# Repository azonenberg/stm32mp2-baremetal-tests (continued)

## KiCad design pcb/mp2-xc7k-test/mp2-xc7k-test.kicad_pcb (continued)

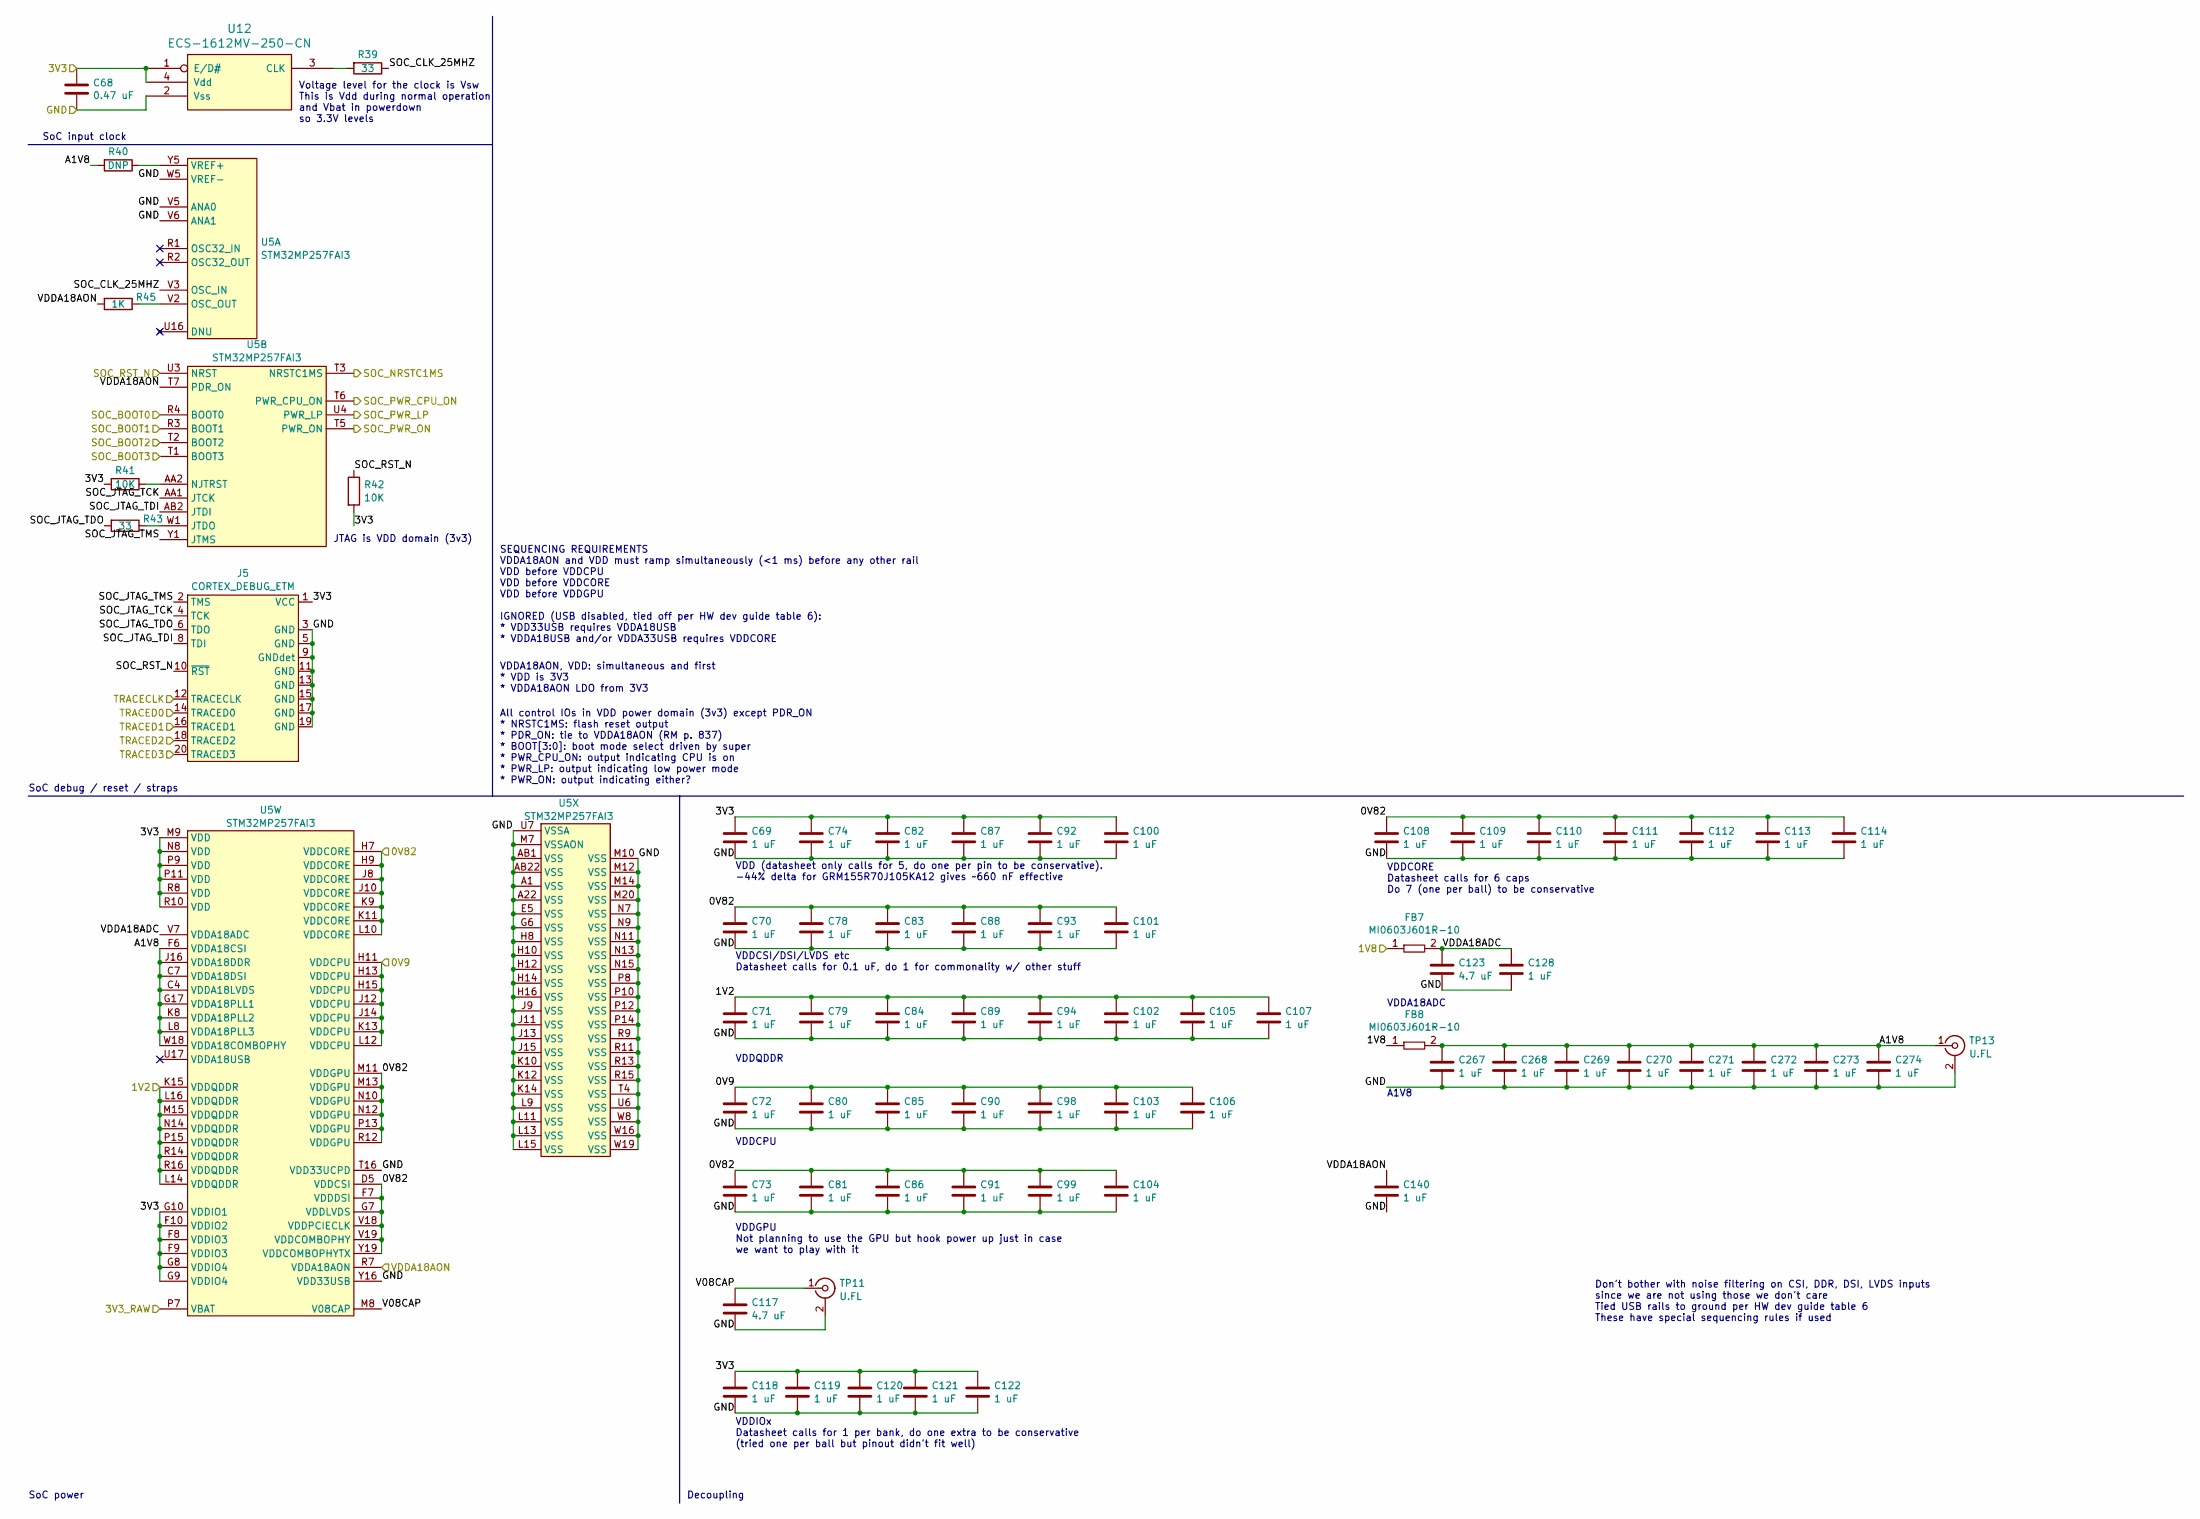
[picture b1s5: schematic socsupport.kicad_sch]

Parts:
C68: 0.47 uF; EIA_0402_CAP_NOSILK
C69, C70, C71, C72, C73, C74, C78, C79, C80, C81, C82, C83, C84, C85, C86, C87, C88, C89, C90, C91, C92, C93, C94, C98, C99, C100, C101, C102, C103, C104, C105, C106, C107, C108, C109, C110, C111, C112, C113, C114, C118, C119, C120, C121, C122, C128, C140, C267, C268, C269, C270, C271, C272, C273, C274: 1 uF; EIA_0201_CAP_NOSILK
C117, C123: 4.7 uF; EIA_0603_CAP_NOSILK
FB7, FB8: MI0603J601R-10; EIA_0603_INDUCTOR_NOSILK
J5: CORTEX_DEBUG_ETM; CONN_HEADER_1.27MM_2x10_SMT_SAMTEC_FTSH-110-01-L-DV-K
R39, R43: 33; EIA_0402_RES_NOSILK
R40: DNP; EIA_0402_RES_NOSILK
R41, R42: 10K; EIA_0402_RES_NOSILK
R45: 1K; EIA_0402_RES_NOSILK
TP11, TP13: U.FL; CONN_U.FL_TE_1909763-1
U5: STM32MP257FAI3; BGA_436_18x18_DEPOP_0.8MM
U12: ECS-1612MV-250-CN; OSCILLATOR_1.6x1.2

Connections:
/0V9: C72.1, C80.1, C85.1, C90.1, C98.1, C103.1, C106.1, U5.H11 (VDDCPU), U5.H13 (VDDCPU), U5.H15 (VDDCPU), U5.J12 (VDDCPU), U5.J14 (VDDCPU), U5.K13 (VDDCPU), U5.L12 (VDDCPU); also elsewhere on the board
/0V82: C70.1, C73.1, C78.1, C81.1, C83.1, C86.1, C88.1, C91.1, C93.1, C99.1, C101.1, C104.1, C108.1, C109.1, C110.1, C111.1, C112.1, C113.1, C114.1, U5.D5 (VDDCSI), U5.F7 (VDDDSI), U5.G7 (VDDLVDS), U5.H7 (VDDCORE), U5.H9 (VDDCORE), U5.J8 (VDDCORE), U5.J10 (VDDCORE), U5.K9 (VDDCORE), U5.K11 (VDDCORE), U5.L10 (VDDCORE), U5.M11 (VDDGPU), U5.M13 (VDDGPU), U5.N10 (VDDGPU), U5.N12 (VDDGPU), U5.P13 (VDDGPU), U5.R12 (VDDGPU), U5.V18 (VDDPCIECLK), U5.V19 (VDDCOMBOPHY), U5.Y19 (VDDCOMBOPHYTX); also elsewhere on the board
/1V2: C71.1, C79.1, C84.1, C89.1, C94.1, C102.1, C105.1, C107.1, U5.K15 (VDDQDDR), U5.L14 (VDDQDDR), U5.L16 (VDDQDDR), U5.M15 (VDDQDDR), U5.N14 (VDDQDDR), U5.P15 (VDDQDDR), U5.R14 (VDDQDDR), U5.R16 (VDDQDDR); also elsewhere on the board
/1V8: FB7.1, FB8.1; also elsewhere on the board
/1V8_2: C140.1, R45.2, U5.R7 (VDDA18AON), U5.T7 (PDR_ON); also elsewhere on the board
/3V3: C68.1, C69.1, C74.1, C82.1, C87.1, C92.1, C100.1, C118.1, C119.1, C120.1, C121.1, C122.1, J5.1 (VCC), R41.2, R42.2, U5.F8 (VDDIO3), U5.F9 (VDDIO3), U5.F10 (VDDIO2), U5.G8 (VDDIO4), U5.G9 (VDDIO4), U5.G10 (VDDIO1), U5.M9 (VDD), U5.N8 (VDD), U5.P9 (VDD), U5.P11 (VDD), U5.R8 (VDD), U5.R10 (VDD), U12.1 (E/D#), U12.4 (Vdd); also elsewhere on the board
/3V3_RAW: U5.P7 (VBAT); also elsewhere on the board
/GND: C68.2, C69.2, C70.2, C71.2, C72.2, C73.2, C74.2, C78.2, C79.2, C80.2, C81.2, C82.2, C83.2, C84.2, C85.2, C86.2, C87.2, C88.2, C89.2, C90.2, C91.2, C92.2, C93.2, C94.2, C98.2, C99.2, C100.2, C101.2, C102.2, C103.2, C104.2, C105.2, C106.2, C107.2, C108.2, C109.2, C110.2, C111.2, C112.2, C113.2, C114.2, C117.2, C118.2, C119.2, C120.2, C121.2, C122.2, C123.2, C128.2, C140.2, C267.2, C268.2, C269.2, C270.2, C271.2, C272.2, C273.2, C274.2, J5.3 (GND), J5.5 (GND), J5.9 (GNDdet), J5.11 (GND), J5.13 (GND), J5.15 (GND), J5.17 (GND), J5.19 (GND), TP11.2 (Ext), TP13.2 (Ext), U5.A1 (VSS), U5.A22 (VSS), U5.AB1 (VSS), U5.AB22 (VSS), U5.E5 (VSS), U5.G6 (VSS), U5.H8 (VSS), U5.H10 (VSS), U5.H12 (VSS), U5.H14 (VSS), U5.H16 (VSS), U5.J9 (VSS), U5.J11 (VSS), U5.J13 (VSS), U5.J15 (VSS), U5.K10 (VSS), U5.K12 (VSS), U5.K14 (VSS), U5.L9 (VSS), U5.L11 (VSS), U5.L13 (VSS), U5.L15 (VSS), U5.M7 (VSSAON), U5.M10 (VSS), U5.M12 (VSS), U5.M14 (VSS), U5.M20 (VSS), U5.N7 (VSS), U5.N9 (VSS), U5.N11 (VSS), U5.N13 (VSS), U5.N15 (VSS), U5.P8 (VSS), U5.P10 (VSS), U5.P12 (VSS), U5.P14 (VSS), U5.R9 (VSS), U5.R11 (VSS), U5.R13 (VSS), U5.R15 (VSS), U5.T4 (VSS), U5.T16 (VDD33UCPD), U5.U6 (VSS), U5.U7 (VSSA), U5.V5 (ANA0), U5.V6 (ANA1), U5.W5 (VREF-), U5.W8 (VSS), U5.W16 (VSS), U5.W19 (VSS), U5.Y16 (VDD33USB), U12.2 (Vss); also elsewhere on the board
/Power supply/SOC_BOOT0: U5.R4 (BOOT0); also elsewhere on the board
/Power supply/SOC_BOOT1: U5.R3 (BOOT1); also elsewhere on the board
/Power supply/SOC_BOOT2: U5.T2 (BOOT2); also elsewhere on the board
/Power supply/SOC_BOOT3: U5.T1 (BOOT3); also elsewhere on the board
/Power supply/SOC_NRST1CMS: U5.T3 (NRSTC1MS); also elsewhere on the board
/Power supply/SOC_PWR_CPU_ON: U5.T6 (PWR_CPU_ON); also elsewhere on the board
/Power supply/SOC_PWR_LP: U5.U4 (PWR_LP); also elsewhere on the board
/Power supply/SOC_PWR_ON: U5.T5 (PWR_ON); also elsewhere on the board
/SoC support/A1V8: C267.1, C268.1, C269.1, C270.1, C271.1, C272.1, C273.1, C274.1, FB8.2, R40.2, TP13.1 (In), U5.C4 (VDDA18LVDS), U5.C7 (VDDA18DSI), U5.F6 (VDDA18CSI), U5.G17 (VDDA18PLL1), U5.J16 (VDDA18DDR), U5.K8 (VDDA18PLL2), U5.L8 (VDDA18PLL3), U5.W18 (VDDA18COMBOPHY)
/SoC support/SOC_CLK_25MHZ: R39.1, U5.V3 (OSC_IN)
/SoC support/SOC_JTAG_TCK: J5.4 (TCK), U5.AA1 (JTCK)
/SoC support/SOC_JTAG_TDI: J5.8 (TDI), U5.AB2 (JTDI)
/SoC support/SOC_JTAG_TDO: J5.6 (TDO), R43.2
/SoC support/SOC_JTAG_TMS: J5.2 (TMS), U5.Y1 (JTMS)
/SoC support/SOC_RST_N: J5.10 (~RST), R42.1, U5.U3 (NRST); also elsewhere on the board
/SoC support/TRACECLK: J5.12 (TRACECLK); also elsewhere on the board
/SoC support/TRACED0: J5.14 (TRACED0); also elsewhere on the board
/SoC support/TRACED1: J5.16 (TRACED1); also elsewhere on the board
/SoC support/TRACED2: J5.18 (TRACED2); also elsewhere on the board
/SoC support/TRACED3: J5.20 (TRACED3); also elsewhere on the board
/SoC support/V08CAP: C117.1, TP11.1 (In), U5.M8 (V08CAP)
/SoC support/VDDA18ADC: C123.1, C128.1, FB7.2, U5.V7 (VDDA18ADC)
unnamed: R45.1, U5.V2 (OSC_OUT)
unnamed: R40.1, U5.Y5 (VREF+)
unnamed: R43.1, U5.W1 (JTDO)
unnamed: R41.1, U5.AA2 (NJTRST)
unnamed: R39.2, U12.3 (CLK)

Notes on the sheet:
VDD (datasheet only calls for 5, do one per pin to be conservative). -44% delta for GRM155R70J105KA12 gives ~660 nF effective
SoC debug / reset / straps
Decoupling
SEQUENCING REQUIREMENTS VDDA18AON and VDD must ramp simultaneously (<1 ms) before any other rail VDD before VDDCPU VDD before VDDCORE VDD before VDDGPU IGNORED (USB disabled, tied off per HW dev guide table 6): * VDD33USB requires VDDA18USB * VDDA18USB and/or VDDA33USB requires VDDCORE
VDDIOx Datasheet calls for 1 per bank, do one extra to be conservative (tried one per ball but pinout didn't fit well)
Voltage level for the clock is Vsw This is Vdd during normal operation and Vbat in powerdown so 3.3V levels
SoC power
VDDCPU
VDDA18AON, VDD: simultaneous and first * VDD is 3V3 * VDDA18AON LDO from 3V3
VDDQDDR
JTAG is VDD domain (3v3)
A1V8
VDDA18ADC
SoC input clock
VDDCORE Datasheet calls for 6 caps Do 7 (one per ball) to be conservative
VDDGPU Not planning to use the GPU but hook power up just in case we want to play with it
All control IOs in VDD power domain (3v3) except PDR_ON * NRSTC1MS: flash reset output * PDR_ON: tie to VDDA18AON (RM p. 837) * BOOT[3:0]: boot mode select driven by super * PWR_CPU_ON: output indicating CPU is on * PWR_LP: output indicating low power mode * PWR_ON: output indicating either?
VDDCSI/DSI/LVDS etc Datasheet calls for 0.1 uF, do 1 for commonality w/ other stuff
Don't bother with noise filtering on CSI, DDR, DSI, LVDS inputs since we are not using those we don't care Tied USB rails to ground per HW dev guide table 6 These have special sequencing rules if used

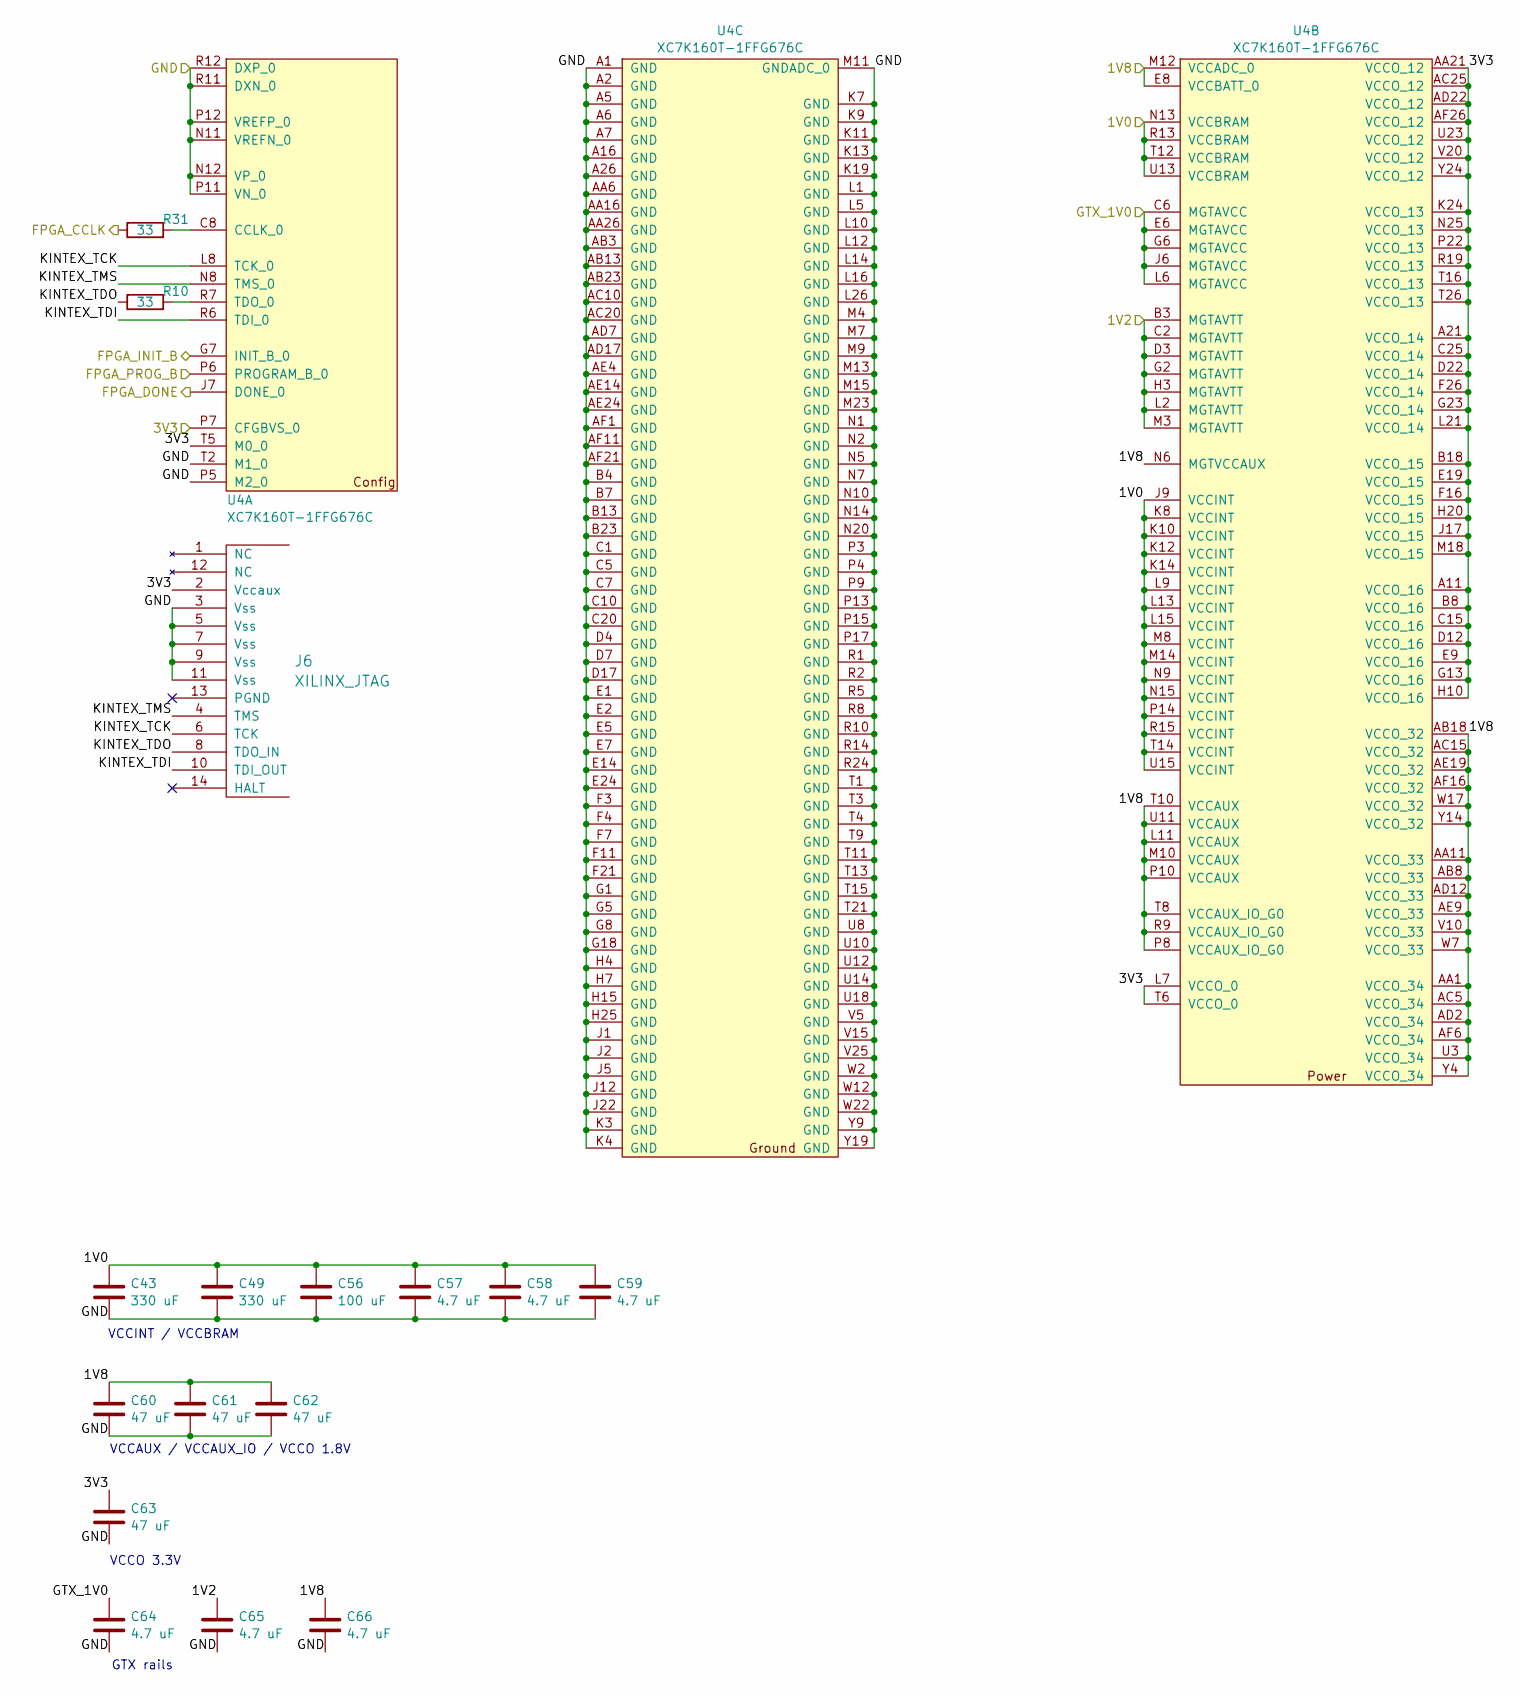
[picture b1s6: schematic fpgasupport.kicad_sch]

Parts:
C43, C49: 330 uF; EIA_1210_CAP_NOSILK
C56: 100 uF; EIA_1210_CAP_NOSILK
C57, C58, C59, C64, C65, C66: 4.7 uF; EIA_0603_CAP_NOSILK
C60, C61, C62, C63: 47 uF; EIA_1210_CAP_NOSILK
J6: XILINX_JTAG; XILINX_JTAG_PTH_MOLEX_0878311420
R10, R31: 33; EIA_0402_RES_NOSILK
U4: XC7K160T-1FFG676C; BGA_676_27x27_FULLARRAY_1MM_FFG676

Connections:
/1V2: C65.1, U4.B3 (MGTAVTT), U4.C2 (MGTAVTT), U4.D3 (MGTAVTT), U4.G2 (MGTAVTT), U4.H3 (MGTAVTT), U4.L2 (MGTAVTT), U4.M3 (MGTAVTT); also elsewhere on the board
/1V8: C60.1, C61.1, C62.1, C66.1, U4.AA1 (VCCO_34), U4.AA11 (VCCO_33), U4.AB8 (VCCO_33), U4.AB18 (VCCO_32), U4.AC5 (VCCO_34), U4.AC15 (VCCO_32), U4.AD2 (VCCO_34), U4.AD12 (VCCO_33), U4.AE9 (VCCO_33), U4.AE19 (VCCO_32), U4.AF6 (VCCO_34), U4.AF16 (VCCO_32), U4.E8 (VCCBATT_0), U4.L11 (VCCAUX), U4.M10 (VCCAUX), U4.M12 (VCCADC_0), U4.N6 (MGTVCCAUX), U4.P8 (VCCAUX_IO_G0), U4.P10 (VCCAUX), U4.R9 (VCCAUX_IO_G0), U4.T8 (VCCAUX_IO_G0), U4.T10 (VCCAUX), U4.U3 (VCCO_34), U4.U11 (VCCAUX), U4.V10 (VCCO_33), U4.W7 (VCCO_33), U4.W17 (VCCO_32), U4.Y4 (VCCO_34), U4.Y14 (VCCO_32); also elsewhere on the board
/3V3: C63.1, J6.2 (Vccaux), U4.A11 (VCCO_16), U4.A21 (VCCO_14), U4.AA21 (VCCO_12), U4.AC25 (VCCO_12), U4.AD22 (VCCO_12), U4.AF26 (VCCO_12), U4.B8 (VCCO_16), U4.B18 (VCCO_15), U4.C15 (VCCO_16), U4.C25 (VCCO_14), U4.D12 (VCCO_16), U4.D22 (VCCO_14), U4.E9 (VCCO_16), U4.E19 (VCCO_15), U4.F16 (VCCO_15), U4.F26 (VCCO_14), U4.G13 (VCCO_16), U4.G23 (VCCO_14), U4.H10 (VCCO_16), U4.H20 (VCCO_15), U4.J17 (VCCO_15), U4.K24 (VCCO_13), U4.L7 (VCCO_0), U4.L21 (VCCO_14), U4.M18 (VCCO_15), U4.N25 (VCCO_13), U4.P7 (CFGBVS_0), U4.P22 (VCCO_13), U4.R19 (VCCO_13), U4.T5 (M0_0), U4.T6 (VCCO_0), U4.T16 (VCCO_13), U4.T26 (VCCO_13), U4.U23 (VCCO_12), U4.V20 (VCCO_12), U4.Y24 (VCCO_12); also elsewhere on the board
/FPGA support/1V0: C43.1, C49.1, C56.1, C57.1, C58.1, C59.1, U4.J9 (VCCINT), U4.K8 (VCCINT), U4.K10 (VCCINT), U4.K12 (VCCINT), U4.K14 (VCCINT), U4.L9 (VCCINT), U4.L13 (VCCINT), U4.L15 (VCCINT), U4.M8 (VCCINT), U4.M14 (VCCINT), U4.N9 (VCCINT), U4.N13 (VCCBRAM), U4.N15 (VCCINT), U4.P14 (VCCINT), U4.R13 (VCCBRAM), U4.R15 (VCCINT), U4.T12 (VCCBRAM), U4.T14 (VCCINT), U4.U13 (VCCBRAM), U4.U15 (VCCINT); also elsewhere on the board
/FPGA support/FPGA_CCLK: R31.1; also elsewhere on the board
/FPGA support/FPGA_DONE: U4.J7 (DONE_0); also elsewhere on the board
/FPGA support/FPGA_INIT_B: U4.G7 (INIT_B_0); also elsewhere on the board
/FPGA support/FPGA_PROG_B: U4.P6 (PROGRAM_B_0); also elsewhere on the board
/FPGA support/GTX_1V0: C64.1, U4.C6 (MGTAVCC), U4.E6 (MGTAVCC), U4.G6 (MGTAVCC), U4.J6 (MGTAVCC), U4.L6 (MGTAVCC); also elsewhere on the board
/FPGA support/KINTEX_TCK: J6.6 (TCK), U4.L8 (TCK_0)
/FPGA support/KINTEX_TDI: J6.10 (TDI_OUT), U4.R6 (TDI_0)
/FPGA support/KINTEX_TDO: J6.8 (TDO_IN), R10.1
/FPGA support/KINTEX_TMS: J6.4 (TMS), U4.N8 (TMS_0)
/GND: C43.2, C49.2, C56.2, C57.2, C58.2, C59.2, C60.2, C61.2, C62.2, C63.2, C64.2, C65.2, C66.2, J6.3 (Vss), J6.5 (Vss), J6.7 (Vss), J6.9 (Vss), J6.11 (Vss), U4.A1 (GND), U4.A2 (GND), U4.A5 (GND), U4.A6 (GND), U4.A7 (GND), U4.A16 (GND), U4.A26 (GND), U4.AA6 (GND), U4.AA16 (GND), U4.AA26 (GND), U4.AB3 (GND), U4.AB13 (GND), U4.AB23 (GND), U4.AC10 (GND), U4.AC20 (GND), U4.AD7 (GND), U4.AD17 (GND), U4.AE4 (GND), U4.AE14 (GND), U4.AE24 (GND), U4.AF1 (GND), U4.AF11 (GND), U4.AF21 (GND), U4.B4 (GND), U4.B7 (GND), U4.B13 (GND), U4.B23 (GND), U4.C1 (GND), U4.C5 (GND), U4.C7 (GND), U4.C10 (GND), U4.C20 (GND), U4.D4 (GND), U4.D7 (GND), U4.D17 (GND), U4.E1 (GND), U4.E2 (GND), U4.E5 (GND), U4.E7 (GND), U4.E14 (GND), U4.E24 (GND), U4.F3 (GND), U4.F4 (GND), U4.F7 (GND), U4.F11 (GND), U4.F21 (GND), U4.G1 (GND), U4.G5 (GND), U4.G8 (GND), U4.G18 (GND), U4.H4 (GND), U4.H7 (GND), U4.H15 (GND), U4.H25 (GND), U4.J1 (GND), U4.J2 (GND), U4.J5 (GND), U4.J12 (GND), U4.J22 (GND), U4.K3 (GND), U4.K4 (GND), U4.K7 (GND), U4.K9 (GND), U4.K11 (GND), U4.K13 (GND), U4.K19 (GND), U4.L1 (GND), U4.L5 (GND), U4.L10 (GND), U4.L12 (GND), U4.L14 (GND), U4.L16 (GND), U4.L26 (GND), U4.M4 (GND), U4.M7 (GND), U4.M9 (GND), U4.M11 (GNDADC_0), U4.M13 (GND), U4.M15 (GND), U4.M23 (GND), U4.N1 (GND), U4.N2 (GND), U4.N5 (GND), U4.N7 (GND), U4.N10 (GND), U4.N11 (VREFN_0), U4.N12 (VP_0), U4.N14 (GND), U4.N20 (GND), U4.P3 (GND), U4.P4 (GND), U4.P5 (M2_0), U4.P9 (GND), U4.P11 (VN_0), U4.P12 (VREFP_0), U4.P13 (GND), U4.P15 (GND), U4.P17 (GND), U4.R1 (GND), U4.R2 (GND), U4.R5 (GND), U4.R8 (GND), U4.R10 (GND), U4.R11 (DXN_0), U4.R12 (DXP_0), U4.R14 (GND), U4.R24 (GND), U4.T1 (GND), U4.T2 (M1_0), U4.T3 (GND), U4.T4 (GND), U4.T9 (GND), U4.T11 (GND), U4.T13 (GND), U4.T15 (GND), U4.T21 (GND), U4.U8 (GND), U4.U10 (GND), U4.U12 (GND), U4.U14 (GND), U4.U18 (GND), U4.V5 (GND), U4.V15 (GND), U4.V25 (GND), U4.W2 (GND), U4.W12 (GND), U4.W22 (GND), U4.Y9 (GND), U4.Y19 (GND); also elsewhere on the board
unnamed: R31.2, U4.C8 (CCLK_0)
unnamed: R10.2, U4.R7 (TDO_0)

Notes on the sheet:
VCCO 3.3V
GTX rails
VCCAUX / VCCAUX_IO / VCCO 1.8V
VCCINT / VCCBRAM

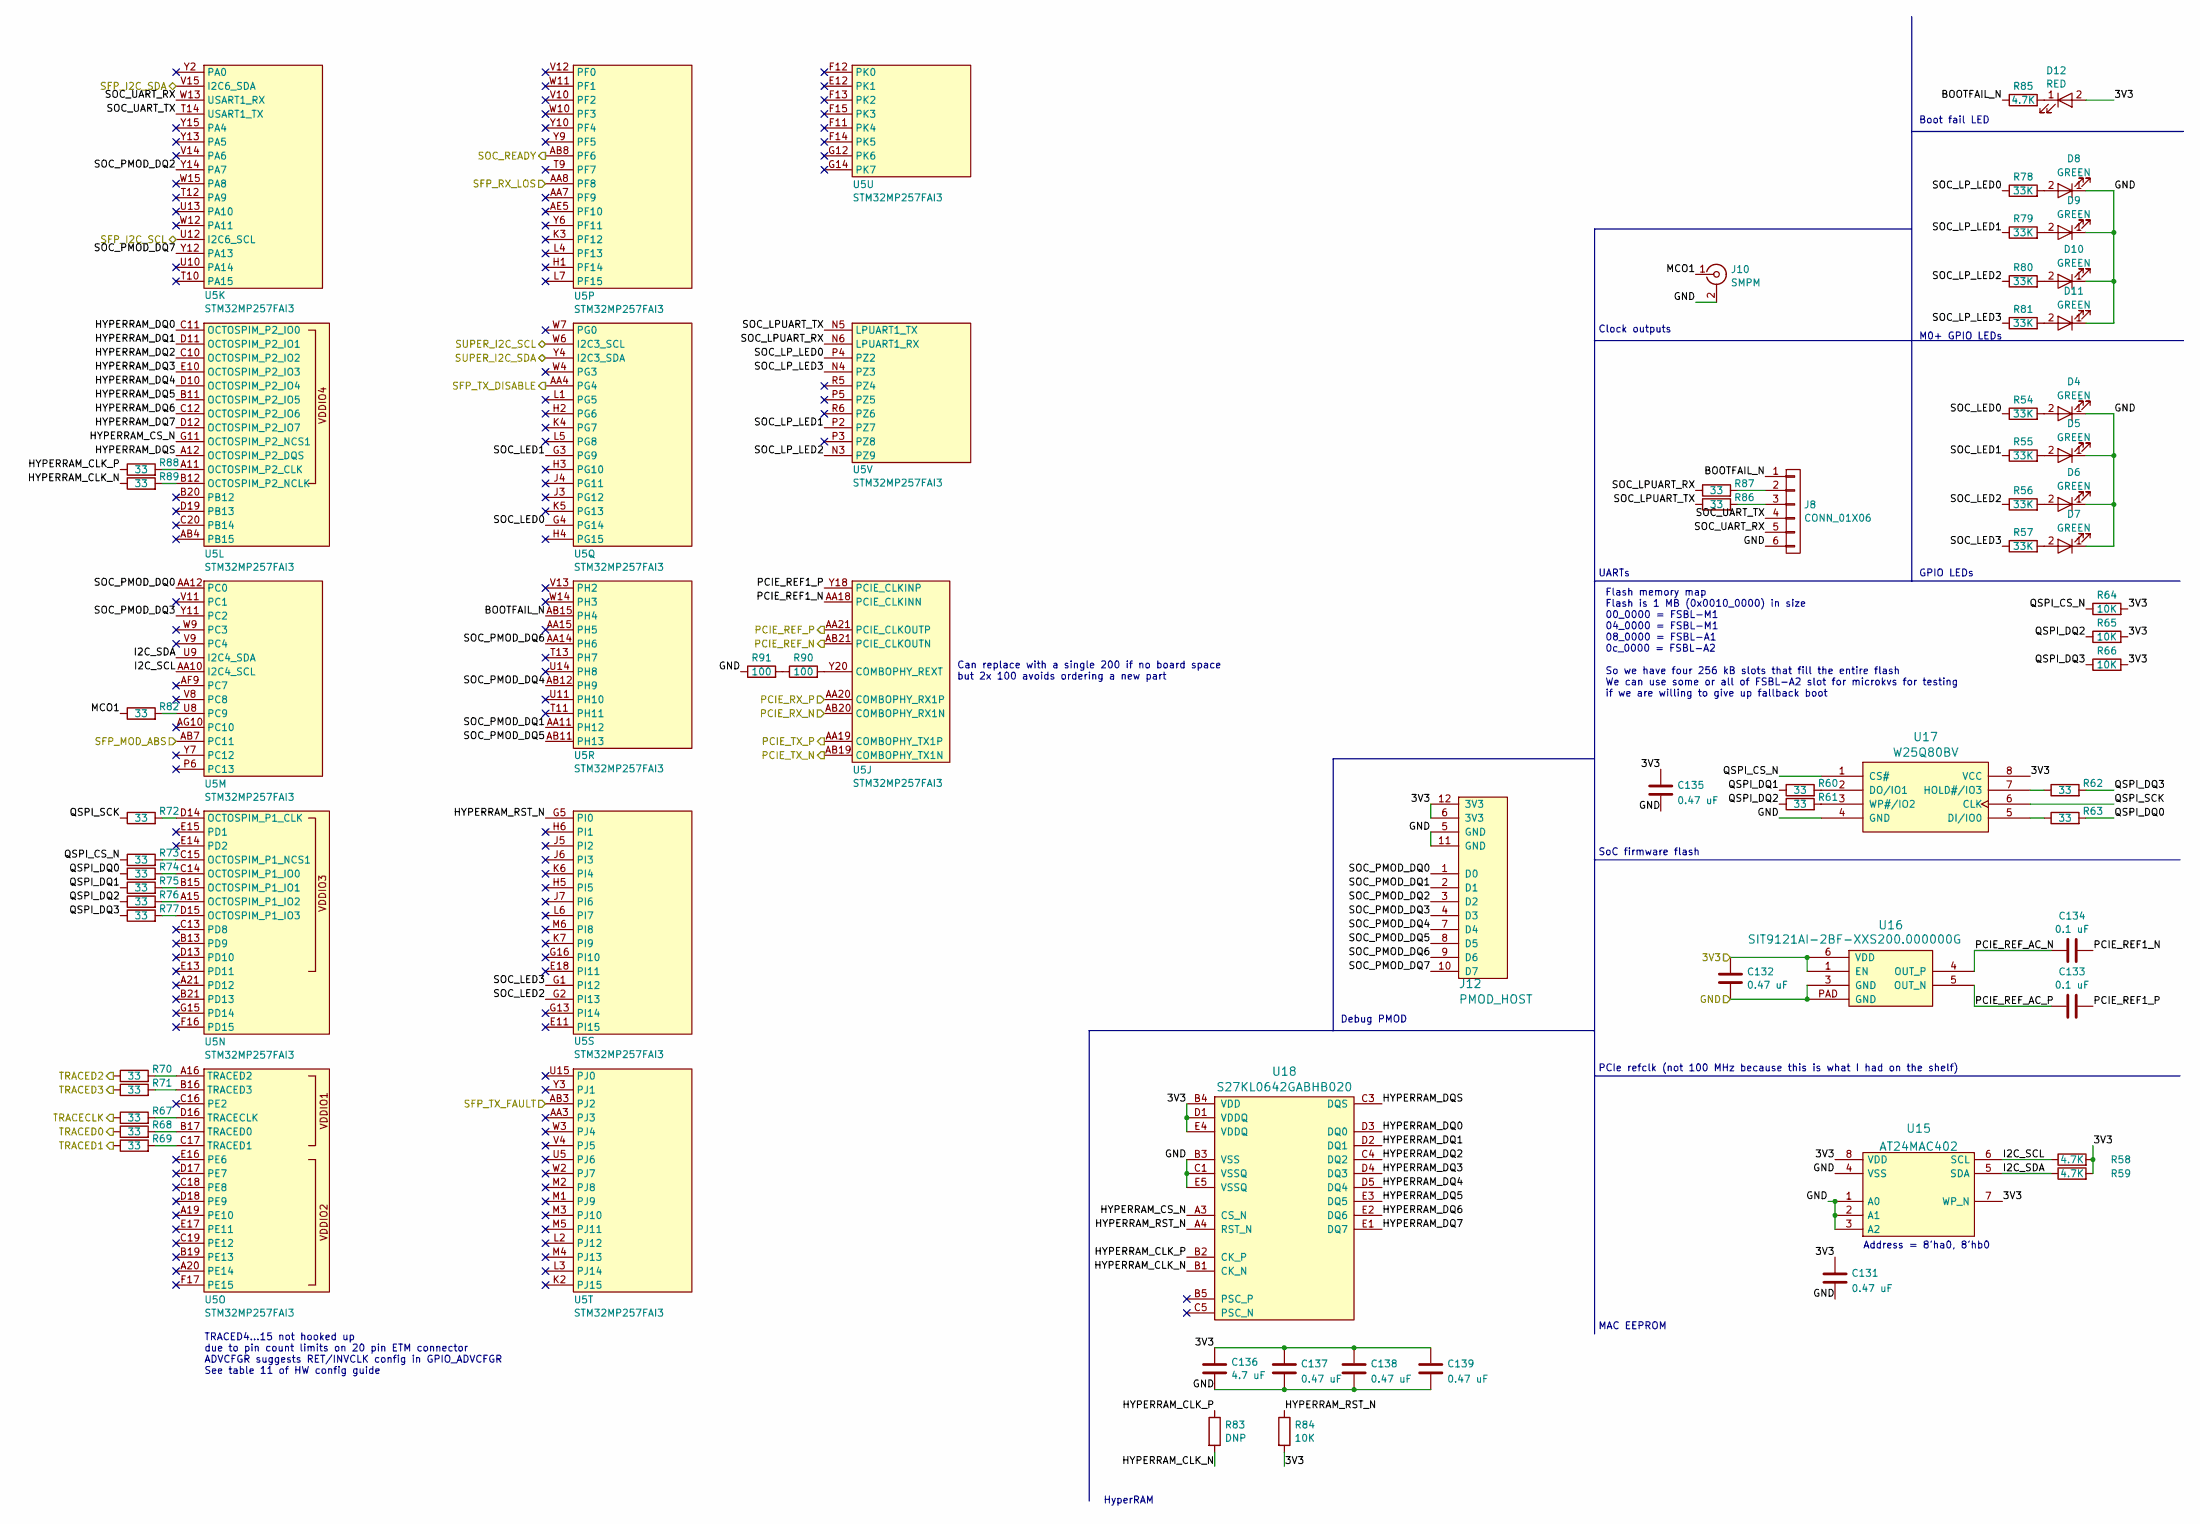
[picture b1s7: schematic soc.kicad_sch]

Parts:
C131, C132, C135, C137, C138, C139: 0.47 uF; EIA_0402_CAP_NOSILK
C133, C134: 0.1 uF; EIA_0402_CAP_NOSILK
C136: 4.7 uF; EIA_0603_CAP_NOSILK
D4, D5, D6, D7, D8, D9, D10, D11: GREEN; EIA_0402_LED
D12: RED; EIA_0402_LED
J8: CONN_01X06; CONN_HEADER_2.54MM_1x6_REFLOW
J10: SMPM; CONN_SMPM_AMPHENOL_C925-197J-51PT
J12: PMOD_HOST; CONN_HEADER_2.54MM_2x6_RA_PMOD_HOST
R54, R55, R56, R57, R78, R79, R80, R81: 33K; EIA_0402_RES_NOSILK
R58, R59, R85: 4.7K; EIA_0402_RES_NOSILK
R60, R61, R62, R63, R67, R68, R69, R70, R71, R72, R73, R74, R75, R76, R77, R82, R86, R87, R88, R89: 33; EIA_0402_RES_NOSILK
R64, R65, R66, R84: 10K; EIA_0402_RES_NOSILK
R83: DNP; EIA_0402_RES_NOSILK
R90, R91: 100; EIA_0402_RES_NOSILK
U5: STM32MP257FAI3; BGA_436_18x18_DEPOP_0.8MM
U15: AT24MAC402; DFN_8_0.5MM_2x3MM_TALL
U16: SIT9121AI-2BF-XXS200.000000G; OSCILLATOR_LVDS_3.2x2.5
U17: W25Q80BV; SOIC_8_5.3MM
U18: S27KL0642GABHB020; BGA_24_6x8_DEPOP1_1MM

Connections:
/3V3: C131.1, C132.1, C135.1, C136.1, C137.1, C138.1, C139.1, D12.2 (A), J12.6 (3V3), J12.12 (3V3), R58.2, R59.2, R64.2, R65.2, R66.2, R84.2, U15.7 (WP_N), U15.8 (VDD), U16.1 (EN), U16.6 (VDD), U17.8 (VCC), U18.B4 (VDD), U18.D1 (VDDQ), U18.E4 (VDDQ); also elsewhere on the board
/FPGA/PCIE_REF_N: U5.AB21 (PCIE_CLKOUTN); also elsewhere on the board
/FPGA/PCIE_REF_P: U5.AA21 (PCIE_CLKOUTP); also elsewhere on the board
/FPGA/PCIE_RX_N: U5.AB20 (COMBOPHY_RX1N); also elsewhere on the board
/FPGA/PCIE_RX_P: U5.AA20 (COMBOPHY_RX1P); also elsewhere on the board
/FPGA/PCIE_TX_N: U5.AB19 (COMBOPHY_TX1N); also elsewhere on the board
/FPGA/PCIE_TX_P: U5.AA19 (COMBOPHY_TX1P); also elsewhere on the board
/FPGA/SFP_I2C_SCL: U5.U12 (I2C6_SCL); also elsewhere on the board
/FPGA/SFP_I2C_SDA: U5.V15 (I2C6_SDA); also elsewhere on the board
/FPGA/SFP_MOD_ABS: U5.AB7 (PC11); also elsewhere on the board
/FPGA/SFP_RX_LOS: U5.AA8 (PF8); also elsewhere on the board
/FPGA/SFP_TX_DISABLE: U5.AA4 (PG4); also elsewhere on the board
/FPGA/SFP_TX_FAULT: U5.AB3 (PJ2); also elsewhere on the board
/GND: C131.2, C132.2, C135.2, C136.2, C137.2, C138.2, C139.2, D4.1 (K), D5.1 (K), D6.1 (K), D7.1 (K), D8.1 (K), D9.1 (K), D10.1 (K), D11.1 (K), J8.6, J10.2 (Ext), J12.5 (GND), J12.11 (GND), R91.1, U15.1 (A0), U15.2 (A1), U15.3 (A2), U15.4 (VSS), U16.3 (GND), U16.PAD (GND), U17.4 (GND), U18.B3 (VSS), U18.C1 (VSSQ), U18.E5 (VSSQ); also elsewhere on the board
/Power supply/SOC_READY: U5.AB8 (PF6); also elsewhere on the board
/Power supply/SUPER_I2C_SCL: U5.W6 (I2C3_SCL); also elsewhere on the board
/Power supply/SUPER_I2C_SDA: U5.Y4 (I2C3_SDA); also elsewhere on the board
/SoC support/TRACECLK: R67.1; also elsewhere on the board
/SoC support/TRACED0: R68.1; also elsewhere on the board
/SoC support/TRACED1: R69.1; also elsewhere on the board
/SoC support/TRACED2: R70.1; also elsewhere on the board
/SoC support/TRACED3: R71.1; also elsewhere on the board
/SoC/BOOTFAIL_N: J8.1, R85.1, U5.AB15 (PH4)
/SoC/HYPERRAM_CLK_N: R83.2, R89.1, U18.B1 (CK_N)
/SoC/HYPERRAM_CLK_P: R83.1, R88.1, U18.B2 (CK_P)
/SoC/HYPERRAM_CS_N: U5.G11 (OCTOSPIM_P2_NCS1), U18.A3 (CS_N)
/SoC/HYPERRAM_DQ0: U5.C11 (OCTOSPIM_P2_IO0), U18.D3 (DQ0)
/SoC/HYPERRAM_DQ1: U5.D11 (OCTOSPIM_P2_IO1), U18.D2 (DQ1)
/SoC/HYPERRAM_DQ2: U5.C10 (OCTOSPIM_P2_IO2), U18.C4 (DQ2)
/SoC/HYPERRAM_DQ3: U5.E10 (OCTOSPIM_P2_IO3), U18.D4 (DQ3)
/SoC/HYPERRAM_DQ4: U5.D10 (OCTOSPIM_P2_IO4), U18.D5 (DQ4)
/SoC/HYPERRAM_DQ5: U5.B11 (OCTOSPIM_P2_IO5), U18.E3 (DQ5)
/SoC/HYPERRAM_DQ6: U5.C12 (OCTOSPIM_P2_IO6), U18.E2 (DQ6)
/SoC/HYPERRAM_DQ7: U5.D12 (OCTOSPIM_P2_IO7), U18.E1 (DQ7)
/SoC/HYPERRAM_DQS: U5.A12 (OCTOSPIM_P2_DQS), U18.C3 (DQS)
/SoC/HYPERRAM_RST_N: R84.1, U5.G5 (PI0), U18.A4 (RST_N)
/SoC/I2C_SCL: R58.1, U5.AA10 (I2C4_SCL), U15.6 (SCL)
/SoC/I2C_SDA: R59.1, U5.U9 (I2C4_SDA), U15.5 (SDA)
/SoC/MCO1: J10.1 (In), R82.1
/SoC/PCIE_REF1_N: C134.2, U5.AA18 (PCIE_CLKINN)
/SoC/PCIE_REF1_P: C133.2, U5.Y18 (PCIE_CLKINP)
/SoC/PCIE_REF_AC_N: C134.1, U16.4 (OUT_P)
/SoC/PCIE_REF_AC_P: C133.1, U16.5 (OUT_N)
/SoC/QSPI_CS_N: R64.1, R73.1, U17.1 (CS#)
/SoC/QSPI_DQ0: R63.2, R74.1
/SoC/QSPI_DQ1: R60.1, R75.1
/SoC/QSPI_DQ2: R61.1, R65.1, R76.1
/SoC/QSPI_DQ3: R62.2, R66.1, R77.1
/SoC/QSPI_SCK: R72.1, U17.6 (CLK)
/SoC/SOC_LED0: R54.1, U5.G4 (PG14)
/SoC/SOC_LED1: R55.1, U5.G3 (PG9)
/SoC/SOC_LED2: R56.1, U5.G2 (PI13)
/SoC/SOC_LED3: R57.1, U5.G1 (PI12)
/SoC/SOC_LPUART_RX: R87.1, U5.N6 (LPUART1_RX)
/SoC/SOC_LPUART_TX: R86.1, U5.N5 (LPUART1_TX)
/SoC/SOC_LP_LED0: R78.1, U5.P4 (PZ2)
/SoC/SOC_LP_LED1: R79.1, U5.P2 (PZ7)
/SoC/SOC_LP_LED2: R80.1, U5.N3 (PZ9)
/SoC/SOC_LP_LED3: R81.1, U5.N4 (PZ3)
/SoC/SOC_PMOD_DQ0: J12.1 (D0), U5.AA12 (PC0)
/SoC/SOC_PMOD_DQ1: J12.2 (D1), U5.AA11 (PH12)
/SoC/SOC_PMOD_DQ2: J12.3 (D2), U5.Y14 (PA7)
/SoC/SOC_PMOD_DQ3: J12.4 (D3), U5.Y11 (PC2)
/SoC/SOC_PMOD_DQ4: J12.7 (D4), U5.AB12 (PH9)
/SoC/SOC_PMOD_DQ5: J12.8 (D5), U5.AB11 (PH13)
/SoC/SOC_PMOD_DQ6: J12.9 (D6), U5.AA14 (PH6)
/SoC/SOC_PMOD_DQ7: J12.10 (D7), U5.Y12 (PA13)
/SoC/SOC_UART_RX: J8.5, U5.W13 (USART1_RX)
/SoC/SOC_UART_TX: J8.4, U5.T14 (USART1_TX)
unnamed: D4.2 (A), R54.2
unnamed: D5.2 (A), R55.2
unnamed: D6.2 (A), R56.2
unnamed: D7.2 (A), R57.2
unnamed: D8.2 (A), R78.2
unnamed: D9.2 (A), R79.2
unnamed: D10.2 (A), R80.2
unnamed: D11.2 (A), R81.2
unnamed: D12.1 (K), R85.2
unnamed: J8.2, R87.2
unnamed: J8.3, R86.2
unnamed: R90.1, R91.2
unnamed: R90.2, U5.Y20 (COMBOPHY_REXT)
unnamed: R88.2, U5.A11 (OCTOSPIM_P2_CLK)
unnamed: R89.2, U5.B12 (OCTOSPIM_P2_NCLK)
unnamed: R82.2, U5.U8 (PC9)
unnamed: R72.2, U5.D14 (OCTOSPIM_P1_CLK)
unnamed: R73.2, U5.C15 (OCTOSPIM_P1_NCS1)
unnamed: R74.2, U5.C14 (OCTOSPIM_P1_IO0)
unnamed: R75.2, U5.B15 (OCTOSPIM_P1_IO1)
unnamed: R76.2, U5.A15 (OCTOSPIM_P1_IO2)
unnamed: R77.2, U5.D15 (OCTOSPIM_P1_IO3)
unnamed: R70.2, U5.A16 (TRACED2)
unnamed: R71.2, U5.B16 (TRACED3)
unnamed: R67.2, U5.D16 (TRACECLK)
unnamed: R68.2, U5.B17 (TRACED0)
unnamed: R69.2, U5.C17 (TRACED1)
unnamed: R63.1, U17.5 (DI/IO0)
unnamed: R60.2, U17.2 (DO/IO1)
unnamed: R62.1, U17.7 (HOLD#/IO3)
unnamed: R61.2, U17.3 (WP#/IO2)

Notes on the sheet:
Debug PMOD
TRACED4...15 not hooked up due to pin count limits on 20 pin ETM connector ADVCFGR suggests RET/INVCLK config in GPIO_ADVCFGR See table 11 of HW config guide
SoC firmware flash
Can replace with a single 200 if no board space but 2x 100 avoids ordering a new part
Flash memory map Flash is 1 MB (0x0010_0000) in size 00_0000 = FSBL-M1 04_0000 = FSBL-M1 08_0000 = FSBL-A1 0c_0000 = FSBL-A2 So we have four 256 kB slots that fill the entire flash We can use some or all of FSBL-A2 slot for microkvs for testing if we are willing to give up fallback boot
M0+ GPIO LEDs
Address = 8'ha0, 8'hb0
Boot fail LED
HyperRAM
Clock outputs
PCIe refclk (not 100 MHz because this is what I had on the shelf)
GPIO LEDs
UARTs
MAC EEPROM

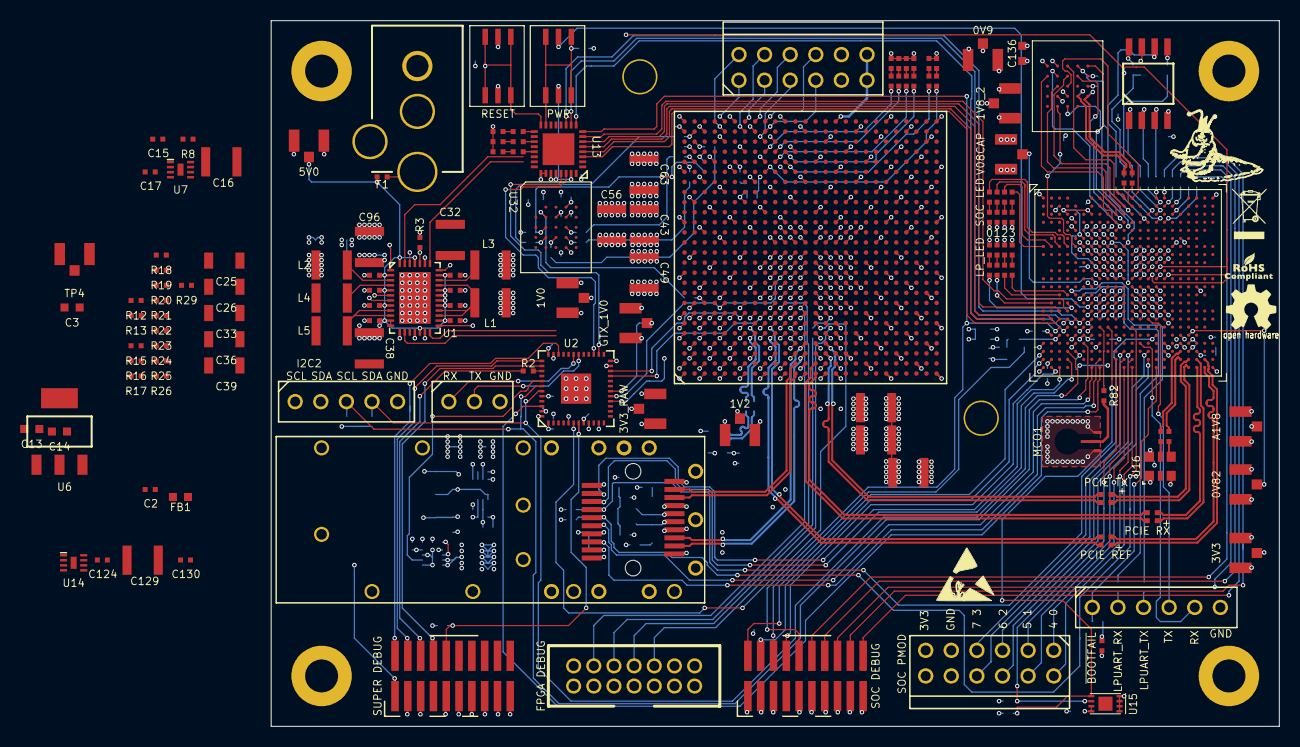
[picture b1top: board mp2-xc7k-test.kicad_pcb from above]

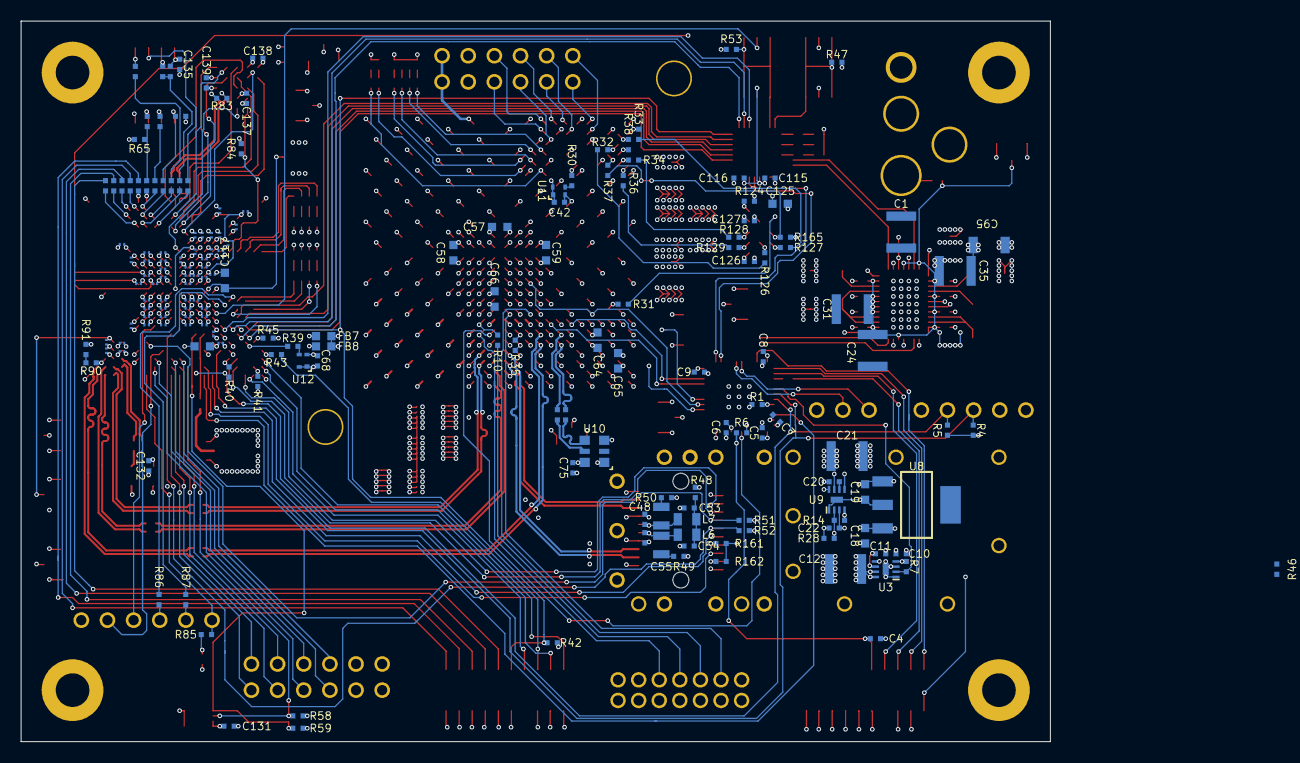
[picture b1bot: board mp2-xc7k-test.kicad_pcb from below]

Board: 4 copper layers, 100.0 x 70.0 mm, 334 parts (180 on the bottom side), 247 nets.

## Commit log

2025-11-07 Initial test firmware for M33
2025-11-07 Blinky
2025-11-07 Added standard submodules
2025-11-16 Initial dummy LED firmware running on CPU2 via SWD runtime programming
2025-11-17 MP2 UART is now alive on testbed
2025-11-18 Now able to detect QSPI flash on the board
2025-11-19 Test firmware is now able to boot from spi flash
2025-11-22 Can now run infinite loop on A35
2025-11-23 Now have per core test code running in asm
2025-11-24 Saving state before cmake-ification of test code
2025-11-25 Addding startup.S state before deleting it
2025-11-28 Initial multicore logging test
2025-11-28 Enabled caches on CPU2
2025-11-29 Initial MMU bringup
2025-11-30 Now using level 2 page table for 0 to 3
2025-11-30 Now have multilevel page tables working
2025-12-01 Caches enables
2025-12-07 Udated submodules
2025-12-07 Added RISAF monitor task
2025-12-07 Fixed typo in default hostname
2025-12-07 Updated submodules
2025-12-07 Make inter-core log buffer size configurable
2025-12-07 CPU2: added RISAF configuration
2025-12-07 Updated to latest stm32-cpp
2025-12-07 Updated log buffer size on A35 side
2025-12-07 Current WIP PCIe bringup
2025-12-20 Continued PCIe bringup work
2025-12-20 Initial version of test PCB schematic
2025-12-22 Continued layout, 454 unrouted
2025-12-23 Continued PCB routing, 344 nets left
2025-12-23 111 unrouted, getting close
2025-12-26 Test board ready for design review
2025-12-26 Added missing ground plane cutouts under SFP+ SERDES pairs
2025-12-27 Changed L1 to larger, higher current NRS5030. Reduced inductance from 2.2 uH to 1 per datasheet recommendations
2025-12-27 Schematic review complete, added a few more test points
2025-12-27 Added 1V8_SOC load switch
2025-12-27 Final MP2 XC7K test board ready for fab
2025-12-28 Fixed bad pullup value. Added PnP fixture
